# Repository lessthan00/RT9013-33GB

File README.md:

# RT9013-33GB

[RT9013-33GB](https://www.jlc-smt.com/lcsc/detail?componentCode=C47773)
LDO
VIN 5.5V
VOUT 3.3V
IOUT 0.5A
package SOT-23-5
accuracy 2%
IQ 50uA
VD 250mV@500mA
ENL 0.6V
ENH 1.6V
IEN 0.1uA -> 100K电阻

引脚定义
1-VIN
2-GND
3-EN
4-NC
5-VOUT

## ME6211C33M5G-N board = RT9013-33GB

[ME6211C33M5G-N](https://www.jlc-smt.com/lcsc/detail?componentCode=C82942)
LDO
VIN 6V
VOUT 3.3V
IOUT 300mA
package SOT-23-5
accuracy 2%
IQ 60uA
VD 260mV@200mA
ENL 0.5V
ENH 1V
IEN 应该是uA -> 100K电阻
Vn 50uVrms

引脚定义
1-VIN
2-GND
3-EN
4-NC
5-VOUT

## ME6210A33PG borad change from AMS1117-3V3

[ME6210A33PG](https://www.jlc-smt.com/lcsc/detail?componentCode=C85233)  
LDO  
VIN 18V  
VOUT 3.3V  
IOUT 500mA  
package SOT-89-3  
IQ 2.5uA  
VD 260mV@200mA  

引脚定义  
1-GND  
2-VIN  
3-VOUT  

## HT7550-1 board = ME6210A33PG  

[HT7550-1](https://www.jlc-smt.com/lcsc/detail?componentCode=C5346140)
LDO  
VIN 28V  
VOUT 5V  
IOUT 150mA  
package SOT-89-3
accuracy 2%
IQ 4uA
VD 520mA@100mA  

引脚定义  
1-GND  
2-IN  
3-VOUT  

## ME6206A33XG  borad change from AMS1117-3V3
  
[ME6206A33XG](https://www.jlc-smt.com/lcsc/detail?componentCode=C161345)  
LDO  
VIN 6V  
VOUT 3.3V  
IOUT 300mA  
package SOT-23-3  
IQ 8uA  
VD 400mV@200mA  

引脚定义  
1-GND  
2-VOUT  
3-VIN  

kciad 并无其符号, 根据封装和引脚定义, 选择自MCP1703Ax-330xxTT 这个符号派生  
封装也是取其 Package_TO_SOT_SMD:SOT-23  
输入TVS 改为 SMAJ6.0CA  

## AMS1117-3V3  borad change from HT7333
  
[AMS1117-3V3](https://www.jlc-smt.com/lcsc/detail?componentCode=C5120765)  
LDO  
  
VIN 18V  
VOUT 3.3V  
IOUT 1A  
package SOT-223  
IQ 12mA  
VD 1.4V@1A  
  
引脚引脚定义  
  
1 GND  
2 VOUT  
3 VIN  

输入TVS 改为SMAJ18CA
  
## HT7333  
  
[HT7333](https://item.szlcsc.com/323851.html?fromZone=s_s__%2522HT7333%2522&spm=sc.gb.xh2.zy.n___sc.hm.hd.ss&lcsc_vid=EwQKBQVXRFYIBQVTR1JbVFcAFgRYUl0AFFNZVAEARVQxVlNSQVZWVVFfRVBZXzsOAxUeFF5JWBYZEEoEHg8JSQcJGk4%3D)  
  
LDO  
  
VIN 12V  
VOUT 3.3V  
IOUT 250mA  
package SOT-89-3  
IQ 3uA  
VD 90mV@40mA  
  
引脚定义  
  
1 GND  
2 VIN  
3 VOUT  
  
所以使用kciad 里面的 Regulator_Generic_GND_IN_OUT 生成符号  
  
封装采用PCM_Package_TO_SOT_SMD_AKL:SOT-89-3, 已确认封装焊盘顺序定义无误  
  
## TLV70450DBVR  
  
[TLV70450DBVR](https://www.jlc-smt.com/lcsc/detail?componentCode=C91672)  
VIN 24V  
VOUT 5V  
IOUT 150mA  
IQ 4.5uA  
VD 1.1V@100mA  
package SOT-23-5  
  
1-GND  
2-IN  
3-OUT  
4-NC  
5-NC  
  
这样的封装的引脚定义是很少的,基本上只有TLV70450DBVR,甚至需要自己绘制封装...  

## KP3310SGA

[KP3310SGA](http://www.kiwiinst.com/productinfo/1249602.html)  
高压斩波 + LDOLDO  
VIN 80~305VAC  
VOUT 5V/3.3V/2.7V  
IOUT 30mA  
耐压 650V MOS  
RS(ON) 9.5Ω  
IQ 130uA  
无法获取详细资料,放弃做板子

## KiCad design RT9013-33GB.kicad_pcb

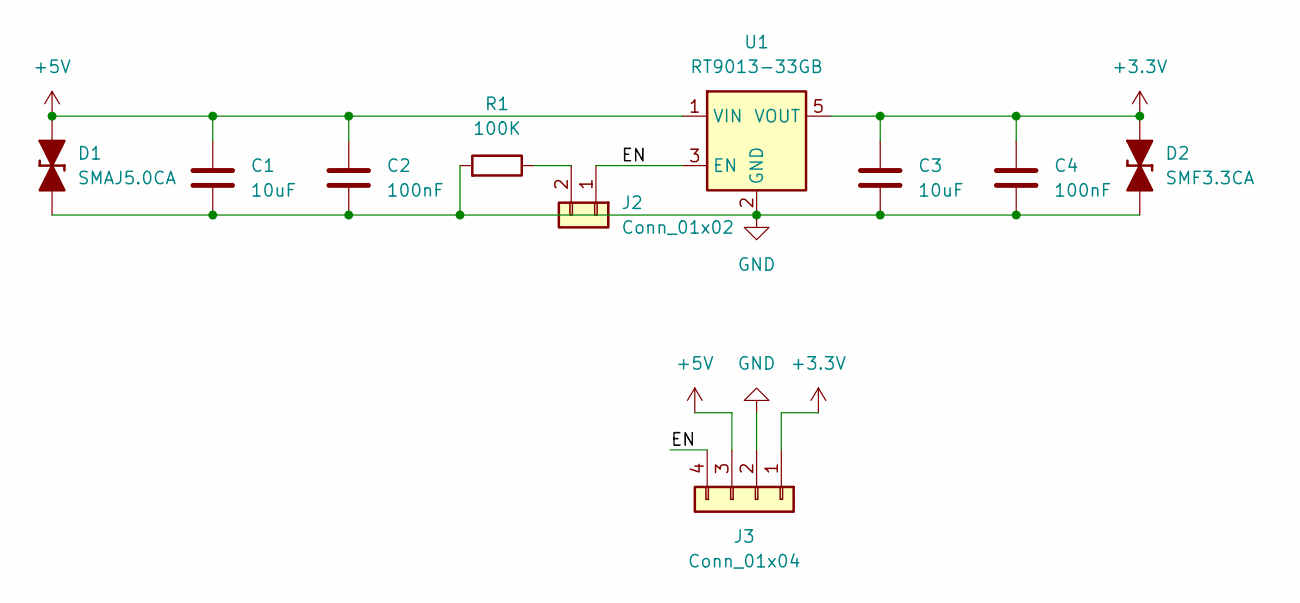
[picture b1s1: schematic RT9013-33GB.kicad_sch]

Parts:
C1, C3: 10uF; C_1206_3216Metric
C2, C4: 100nF; C_1206_3216Metric
D1: SMAJ5.0CA; D_SMA_TVS
D2: SMF3.3CA; D_SOD-123F
J2: Conn_01x02; PinHeader_1x02_P2.54mm_Vertical
J3: Conn_01x04; PinHeader_1x04_P2.54mm_Vertical
R1: 100K; R_1206_3216Metric
U1: RT9013-33GB; SOT-23-5

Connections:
+3.3V: C3.1, C4.1, D2.2 (A), J3.1, U1.5 (VOUT)
+5V: C1.1, C2.1, D1.2 (A), J3.3, U1.1 (VIN)
/EN: J2.1, J3.4, U1.3 (EN)
GND: C1.2, C2.2, C3.2, C4.2, D1.1 (K), D2.1 (K), J3.2, R1.1, U1.2 (GND)
unnamed: J2.2, R1.2

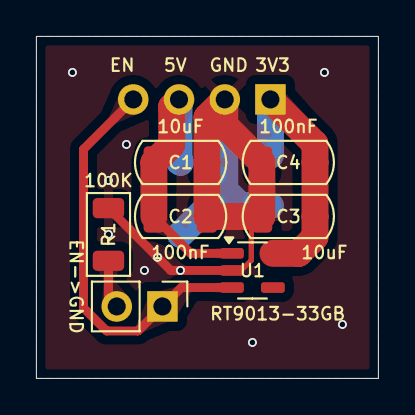
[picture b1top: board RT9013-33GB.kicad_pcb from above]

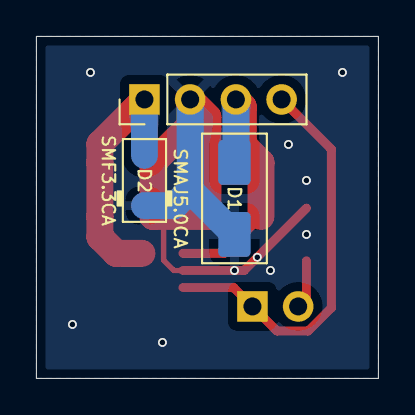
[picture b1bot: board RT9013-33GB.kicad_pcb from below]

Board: 2 copper layers, 19.0 x 19.0 mm, 10 parts (3 on the bottom side), 5 nets.
